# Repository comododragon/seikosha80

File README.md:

# seikosha80
Seikosha80 Chimer Project

Take a look at the [wiki](https://github.com/comododragon/seikosha80/wiki/The-Seikosha80-Project) for the complete story around this project.

**This project is basically end-of-life.** I have found many issues with this PCB, including software instability, battery drainage higher than expected, and so on.

This project will not die though. I have other ideas in mind, perhaps not using RTC anymore. When new stuff arise, I will update here.

Nonetheless, I might still do a bit of work on this board just for some quality improvement. No PCB updates are expected, only software changes. I will use [this](https://github.com/comododragon/seikosha80/wiki/The-Seikosha80-Project#updates) section to group all further updates.

## Revision 1

For a complete description of Revision 1 board, see [here](https://github.com/comododragon/seikosha80/wiki/The-Seikosha80-Project#second-attempt-finally-a-kickoff-2024-).

## PCB

For PCB schematics and layouts, check [here](https://github.com/comododragon/seikosha80/wiki/The-Seikosha80-Project#schematics-and-layouts).

## PCBA

For PCB assemblies, see [here](https://github.com/comododragon/seikosha80/wiki/The-Seikosha80-Project#pcb-assemblies).

## Software

For software description, check [here](https://github.com/comododragon/seikosha80/wiki/The-Seikosha80-Project#the-software).

## Utilities

For the wave conversion and index generation utility, check [here](https://github.com/comododragon/seikosha80/wiki/The-Seikosha80-Project#chime-conversion-and-image-file).

## Next steps

See [here](https://github.com/comododragon/seikosha80/wiki/The-Seikosha80-Project#next-steps).

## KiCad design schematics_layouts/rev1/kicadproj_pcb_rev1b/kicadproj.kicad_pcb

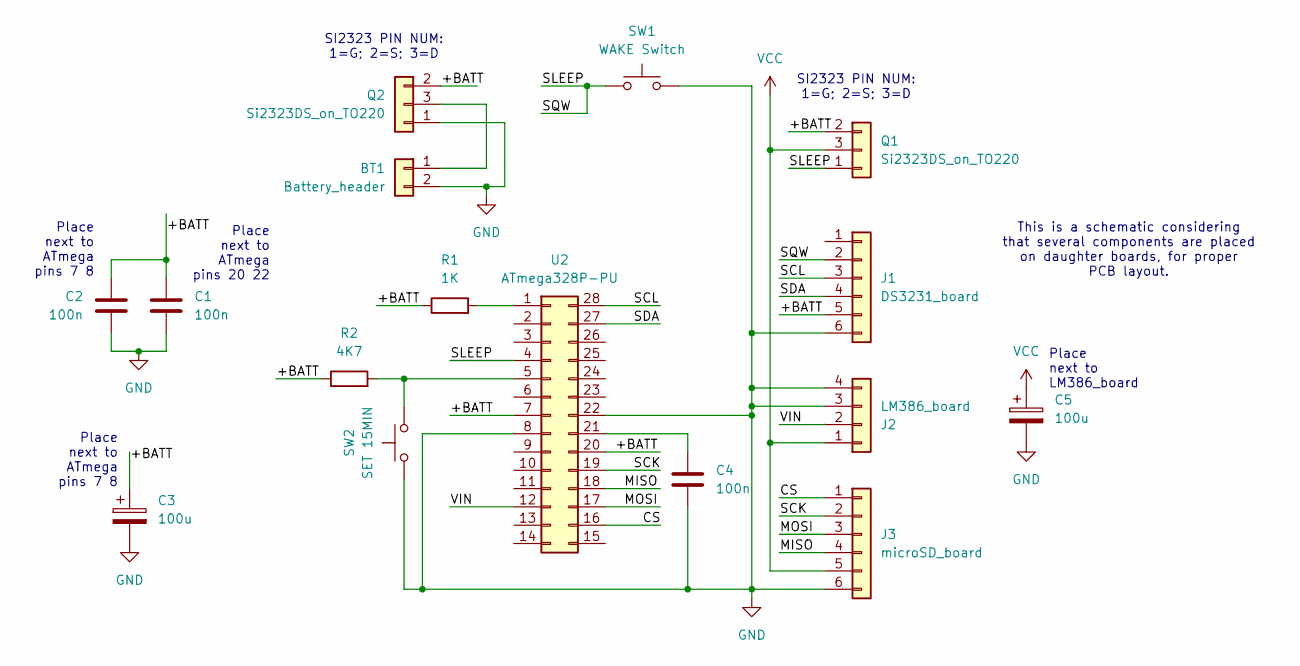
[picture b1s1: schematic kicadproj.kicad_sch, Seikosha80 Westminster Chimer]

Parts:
BT1: Battery_header; PinHeader_1x02_P2.54mm_Vertical
C1: 100n; PinHeader_1x03_P2.54mm_Vertical
C2, C4: 100n; PinHeader_1x02_P2.54mm_Vertical
C3: 100u; PinHeader_1x02_P2.54mm_Vertical
C5: 100u; PinHeader_1x03_P2.54mm_Vertical
J1: DS3231_board; PinHeader_1x06_P2.54mm_Vertical
J2: LM386_board; PinHeader_1x04_P2.54mm_Vertical
J3: microSD_board; PinHeader_1x06_P2.54mm_Vertical
Q1, Q2: Si2323DS_on_TO220; PinHeader_1x03_P2.54mm_Vertical
R1: 1K; PinHeader_1x04_P2.54mm_Vertical
R2: 4K7; PinHeader_1x04_P2.54mm_Vertical
SW1: WAKE Switch; PinHeader_1x03_P2.54mm_Vertical
SW2: SET 15MIN; PinHeader_1x03_P2.54mm_Vertical
U2: ATmega328P-PU; DIP-28_W7.62mm

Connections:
/+BATT: C1.1, C2.1, C3.1, J1.5, Q1.2 (Pin_1), Q2.2 (Pin_1), R1.1, R2.1, U2.7, U2.20
/CS: J3.1, U2.16
/MISO: J3.4, U2.18
/MOSI: J3.3, U2.17
/SCK: J3.2, U2.19
/SCL: J1.3, U2.28
/SDA: J1.4, U2.27
/SLEEP: J1.2, Q1.1 (Pin_3), SW1.1, U2.4
/VIN: J2.2, U2.12
GND: BT1.2, C1.3, C2.2, C3.2, C4.2, C5.3, J1.6, J2.3, J2.4, J3.6, Q2.1 (Pin_3), SW1.3 (2), SW2.3 (2), U2.8, U2.22
unnamed: BT1.1, Q2.3 (Pin_2)
unnamed: R1.4, U2.1
unnamed: R2.4, SW2.1, U2.5
unnamed: C4.1, U2.21
VCC: C5.1, J2.1, J3.5, Q1.3 (Pin_2)

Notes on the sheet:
Place next to LM386_board
Place next to ATmega pins 20 22
SI2323 PIN NUM: 1=G; 2=S; 3=D
This is a schematic considering that several components are placed on daughter boards, for proper PCB layout.
Place next to ATmega pins 7 8

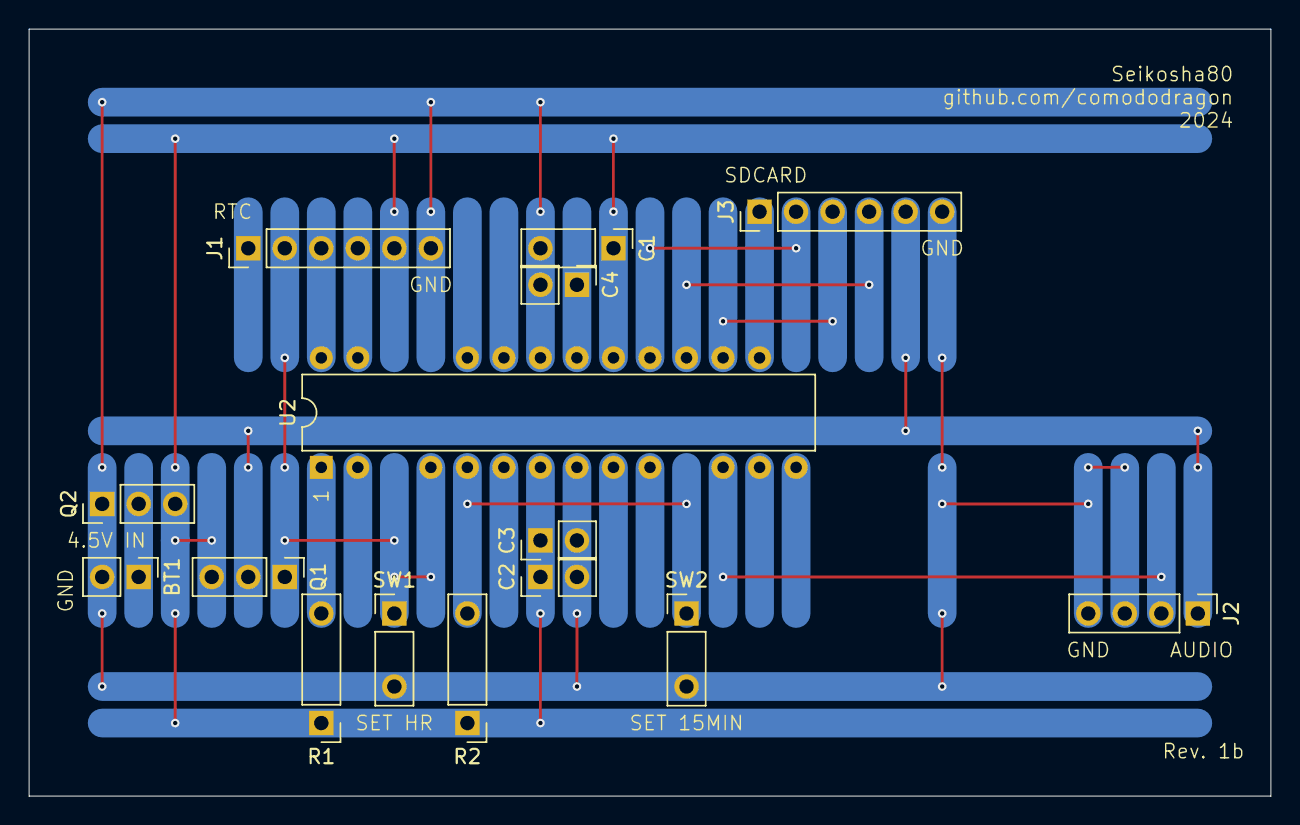
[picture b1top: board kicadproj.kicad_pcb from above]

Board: 2 copper layers, 86.4 x 53.3 mm, 15 parts (0 on the bottom side), 15 nets.

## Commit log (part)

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2024-04-27 Initial commit with most files so far
2024-06-04 Updated schematic with new low-Vgs PFETs and cap on LM386 supply
2024-06-15 Adding a small delay before ATMega goes to sleep
2024-06-16 Adding seiko clock image for Wiki
2024-06-16 Resizing image
2024-06-16 Adding chime pads image
2024-06-16 Adding another image
2024-06-16 More figures
2024-06-16 One more fig
2024-06-17 Adding sdcard figs
2024-06-17 Adding pfet figs
2024-06-26 Potentially fixed the bug that was making the atmega wake up twice; Upsampling to 10kHz
2024-06-26 Adding atmega fig
2024-06-26 Adding atmega figs
2024-06-27 Updating wiki and README; Some folders reorganisation
2024-06-27 Fixing hyperlinks
2024-06-27 Fixing README
2024-06-27 Updated Makefile; Updated wiki page; Fixed PFET names on schematic; Added kicad project for PCB layout
2024-07-03 Updated PCB layout
2024-07-03 Revised PCB layout; Updated documentation
2024-07-04 Revised PCB layout; Created PCB layout revision 1b
2024-07-05 Revised PCB layouts; Created PCB layout revision 1c; Updated docs
2024-07-05 Forgot one fig..
2024-08-14 Revised all docs, removed C5 (never heard about it); Updated wiki with some news
2024-08-23 Replacing placeholders with proper images; Adding section related to NS8002 experiments
2024-08-23 Adding more fig
2024-08-23 Updating README
2024-08-23 Updated schematic for NS8002 (Schematic revision 1b); Updated wiki page and figures
2024-08-23 Fixed small error on schematic for 1b; updated docs
